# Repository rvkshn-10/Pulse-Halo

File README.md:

# Pulse Halo

Pulse Halo is a small desktop audio visualizer built around a 1.28-inch round GC9A01 TFT. A microphone module feeds a XIAO RP2040, which will draw the circular spectrum spikes seen in music-visualizer videos. A rotary encoder controls the display, and six rear-facing WS2812B LEDs add a soft wall/desk glow.

The design target is a complete project under the Hack Club $50 cap, including shipping and tax. Phase 1 deliberately uses inexpensive modules and commonly stocked parts; purchasing and landed-price verification will happen before ordering.

## Project status

- **Phase 1 — KiCad:** complete design package in this repository
- **Phase 2 — Fusion:** not started
- **Phase 3 — firmware, features, and revisions:** not started

This is a design-checked PCB, not a fabricated or hardware-tested board yet.

## Phase 1 hardware

- Seeed Studio XIAO RP2040 controller module
- 1.28-inch 240x240 GC9A01 SPI round TFT module
- 3.3 V analog microphone module
- EC11 rotary encoder with push switch
- Six rear-mounted WS2812B LEDs
- 74AHCT1G125 3.3 V-to-5 V LED data buffer
- 330 ohm WS2812 data resistor
- 100 nF local bypass capacitor and 100 uF LED bulk capacitor
- 58 mm x 58 mm rounded two-layer PCB with four M3 mounting holes

USB powers the XIAO and the board. Firmware must impose a conservative global LED brightness limit so the six LEDs and display stay within the available USB current.

## Repository map

- `hardware/kicad/` — editable KiCad project, local symbol library, and XIAO footprint
- `docs/PHASE-1-KICAD.md` — architecture, pin map, checks, and screenshot index
- `docs/screenshots/phase-1/` — 11 unique progress screenshots
- `docs/exports/Pulse-Halo-schematic.pdf` — readable schematic export
- `manufacturing/gerbers/` — copper, mask, silkscreen, outline, and job files
- `manufacturing/drill/` — PTH/NPTH Excellon files and drill maps
- `manufacturing/assembly/Pulse-Halo-BOM.csv` — generated PCB BOM
- `manufacturing/Pulse-Halo-board.step` — board export for Phase 2 enclosure work

## Validation snapshot

- ERC: 0 errors, 3 warnings. The warnings are cache/library comparison notices for the three project-local symbols.
- DRC: 0 errors, 5 warnings. Four warnings are local mounting-hole footprint/library comparison notices; one is the back-silkscreen D6 reference near the rounded board edge.
- Routing: 0 unrouted nets after routing, with front and rear ground pours.

The warnings and generated fabrication package should be reviewed once more against the exact PCB manufacturer's rules before ordering.

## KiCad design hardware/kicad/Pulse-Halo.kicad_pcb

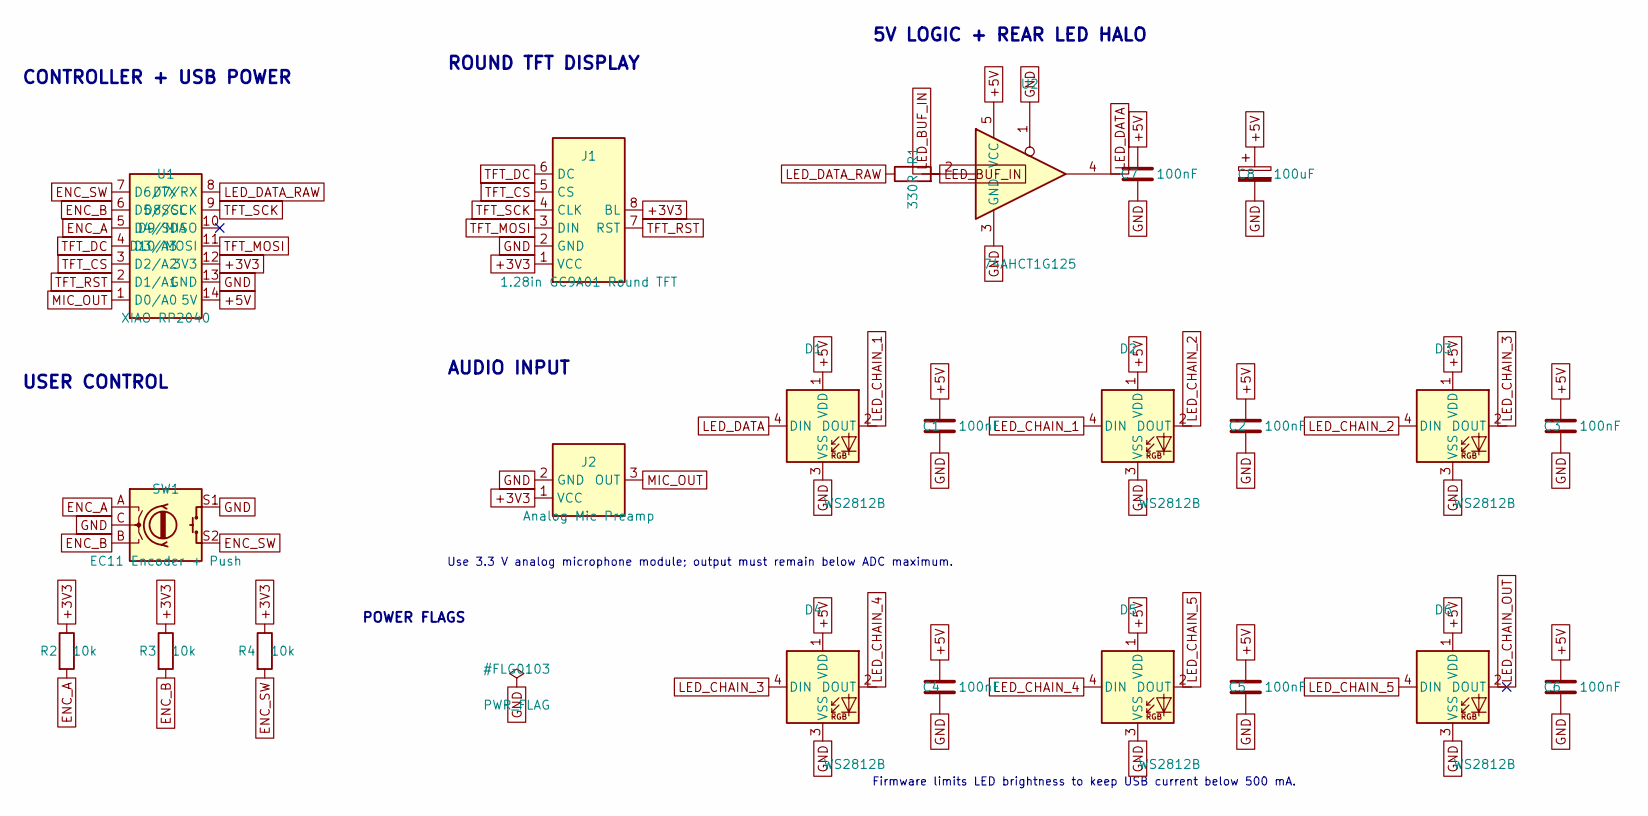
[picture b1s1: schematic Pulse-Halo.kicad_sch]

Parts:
C1, C2, C3, C4, C5, C6, C7: 100nF; C_0603_1608Metric_Pad1.08x0.95mm_HandSolder
C8: 100uF; CP_Radial_D6.3mm_P2.50mm
D1, D2, D3, D4, D5, D6: WS2812B; LED_WS2812B_PLCC4_5.0x5.0mm_P3.2mm
J1: 1.28in GC9A01 Round TFT; JST_PH_B8B-PH-K_1x08_P2.00mm_Vertical
J2: Analog Mic Preamp; PinHeader_1x03_P2.54mm_Vertical
R1: 330R; R_0603_1608Metric_Pad0.98x0.95mm_HandSolder
R2, R3, R4: 10k; R_0603_1608Metric_Pad0.98x0.95mm_HandSolder
SW1: EC11 Encoder + Push; RotaryEncoder_Alps_EC11E-Switch_Vertical_H20mm
U1: XIAO RP2040; XIAO_RP2040_THT
U2: 74AHCT1G125; SOT-23-5_HandSoldering

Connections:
+3V3: J1.1 (VCC), J1.8 (BL), J2.1 (VCC), R2.1, R3.1, R4.1, U1.12 (3V3)
+5V: C1.1, C2.1, C3.1, C4.1, C5.1, C6.1, C7.1, C8.1, D1.1 (VDD), D2.1 (VDD), D3.1 (VDD), D4.1 (VDD), D5.1 (VDD), D6.1 (VDD), U1.14 (5V), U2.5 (VCC)
ENC_A: R2.2, SW1.A, U1.5 (D4/SDA)
ENC_B: R3.2, SW1.B, U1.6 (D5/SCL)
ENC_SW: R4.2, SW1.S2, U1.7 (D6/TX)
GND: C1.2, C2.2, C3.2, C4.2, C5.2, C6.2, C7.2, C8.2, D1.3 (VSS), D2.3 (VSS), D3.3 (VSS), D4.3 (VSS), D5.3 (VSS), D6.3 (VSS), J1.2 (GND), J2.2 (GND), SW1.C, SW1.S1, U1.13 (GND), U2.1, U2.3 (GND)
LED_BUF_IN: R1.2, U2.2
LED_CHAIN_1: D1.2 (DOUT), D2.4 (DIN)
LED_CHAIN_2: D2.2 (DOUT), D3.4 (DIN)
LED_CHAIN_3: D3.2 (DOUT), D4.4 (DIN)
LED_CHAIN_4: D4.2 (DOUT), D5.4 (DIN)
LED_CHAIN_5: D5.2 (DOUT), D6.4 (DIN)
LED_CHAIN_OUT: D6.2 (DOUT)
LED_DATA: D1.4 (DIN), U2.4
LED_DATA_RAW: R1.1, U1.8 (D7/RX)
MIC_OUT: J2.3 (OUT), U1.1 (D0/A0)
TFT_CS: J1.5 (CS), U1.3 (D2/A2)
TFT_DC: J1.6 (DC), U1.4 (D3/A3)
TFT_MOSI: J1.3 (DIN), U1.11 (D10/MOSI)
TFT_RST: J1.7 (RST), U1.2 (D1/A1)
TFT_SCK: J1.4 (CLK), U1.9 (D8/SCK)

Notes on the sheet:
CONTROLLER + USB POWER
ROUND TFT DISPLAY
AUDIO INPUT
USER CONTROL
5V LOGIC + REAR LED HALO
Firmware limits LED brightness to keep USB current below 500 mA.
Use 3.3 V analog microphone module; output must remain below ADC maximum.
POWER FLAGS

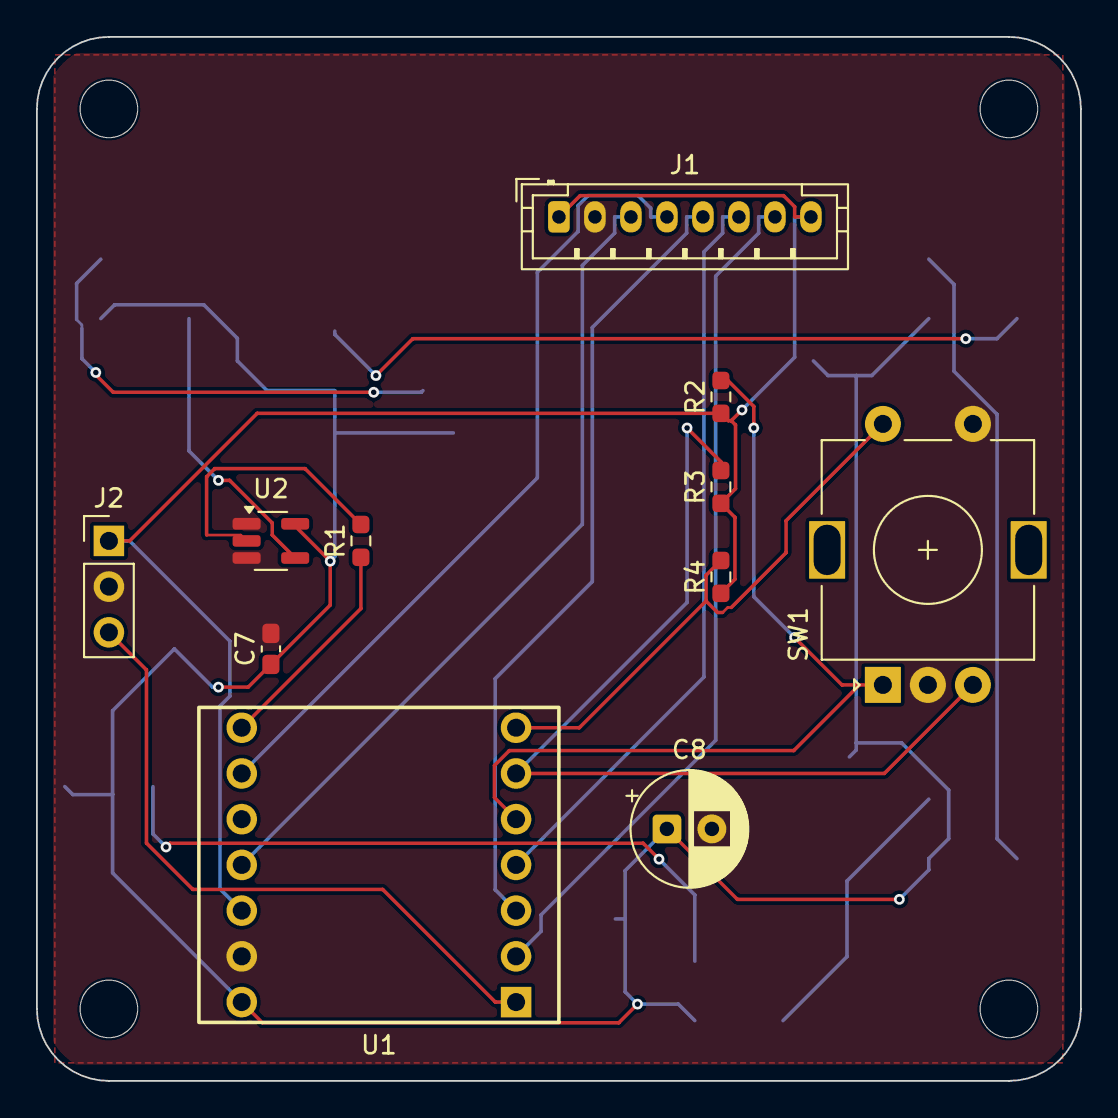
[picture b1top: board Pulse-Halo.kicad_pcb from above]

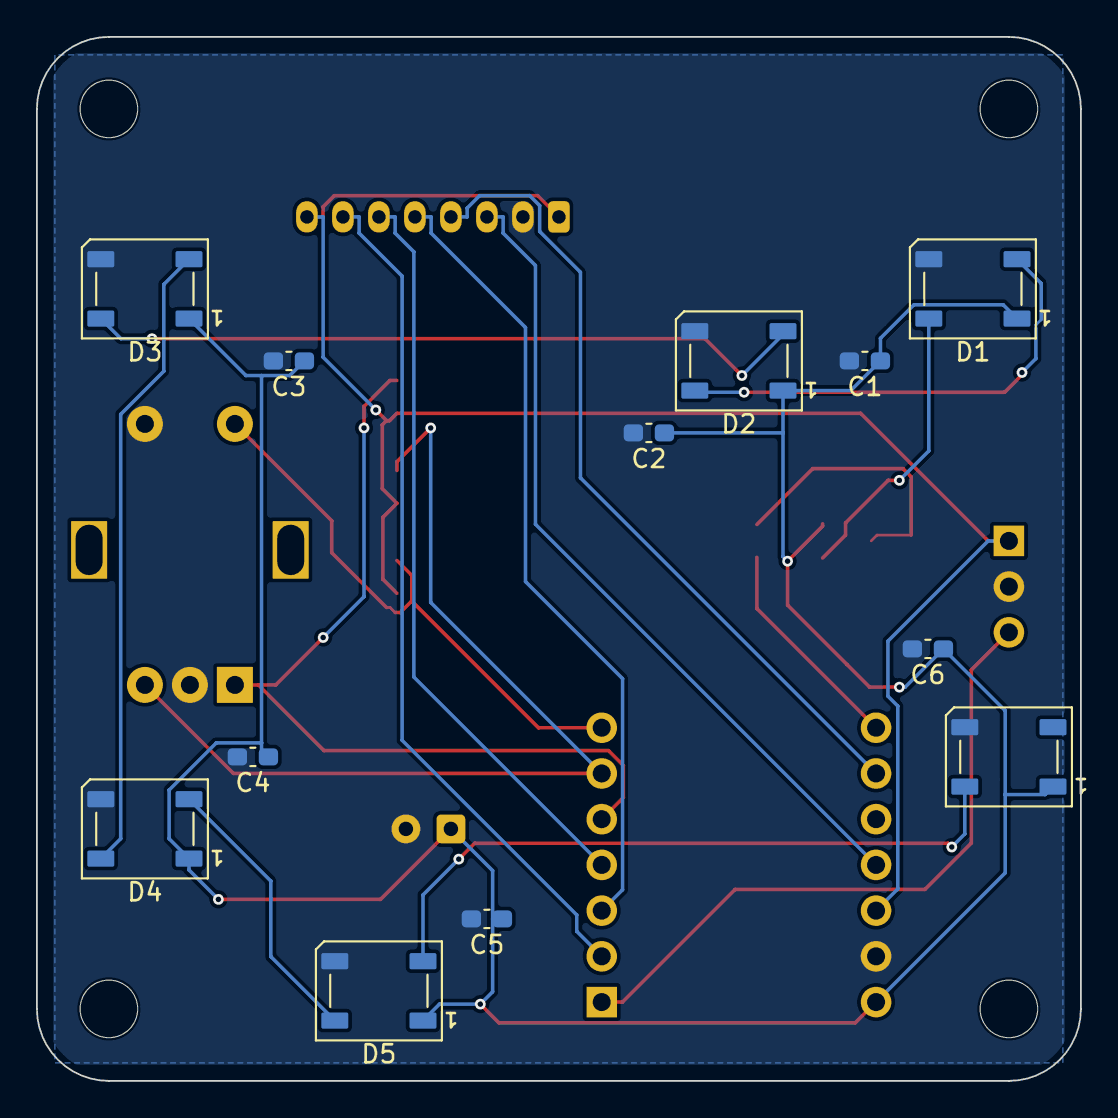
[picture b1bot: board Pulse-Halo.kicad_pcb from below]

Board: 2 copper layers, 58.0 x 58.0 mm, 27 parts (12 on the bottom side), 20 nets.

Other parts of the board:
MH1, MH2, MH3, MH4: MountingHole_3.2mm; MountingHole_3.2mm_M3
